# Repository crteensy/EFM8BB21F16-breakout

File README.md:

# EFM8BB21F16-breakout
A simple breakout board for the EFM8BB21F16 (QFN-20) MCU

The silkscreen might be misleading, clarification below the picture:

The bottom row (starting with Vin) ends with 0.2, 0.1, 0.0, Gnd to the right.
The 4-pin connector located towards the center of the board has 3V3, RSTb (C2CK), 2.0 (C2D), Gnd from left to right.

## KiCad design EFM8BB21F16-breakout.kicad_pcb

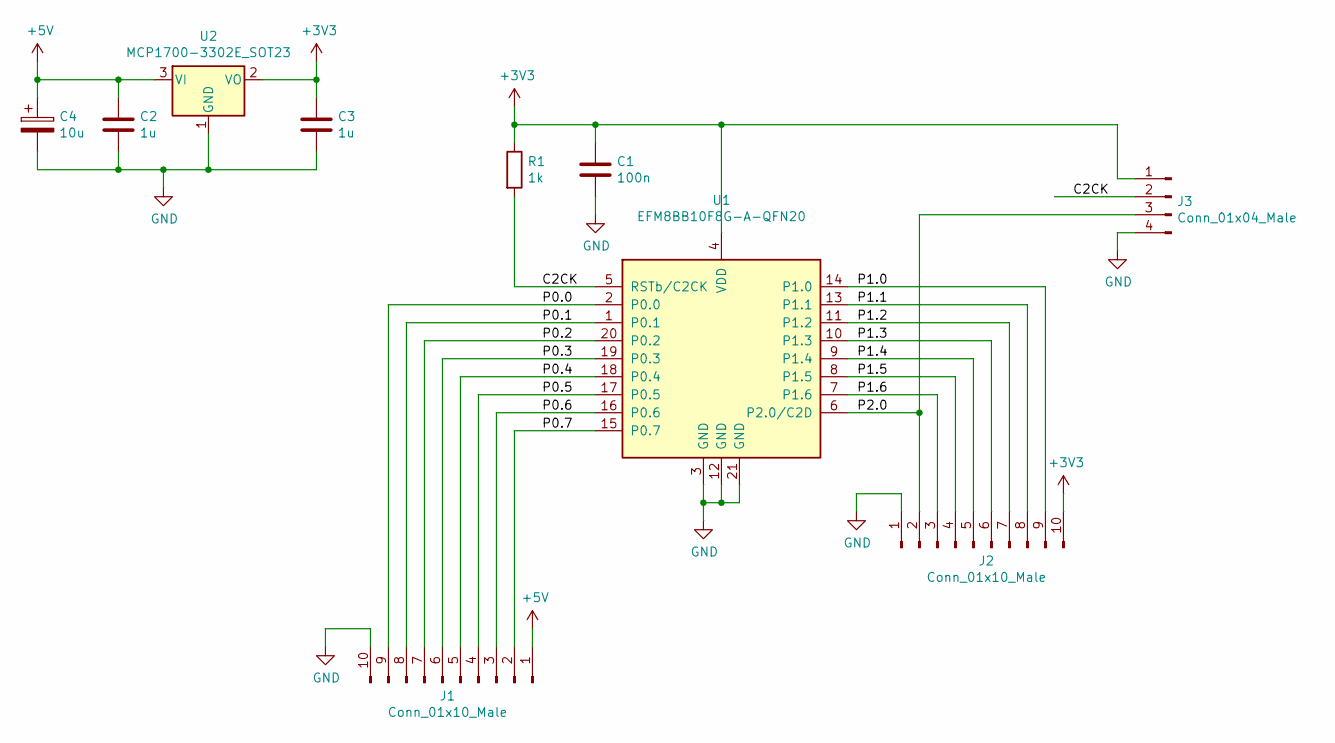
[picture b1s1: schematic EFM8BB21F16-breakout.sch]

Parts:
C1: 100n; C_0603_1608Metric
C2, C3: 1u; C_0603_1608Metric
C4: 10u; C_1206_3216Metric
J1, J2: Conn_01x10_Male; PinHeader_1x10_P2.54mm_Vertical
J3: Conn_01x04_Male; PinHeader_1x04_P2.54mm_Vertical
R1: 1k; R_0603_1608Metric
U1: EFM8BB10F8G-A-QFN20; SiliconLabs_QFN-20-1EP_3x3mm_P0.5mm_ThermalVias
U2: MCP1700-3302E_SOT23; SOT-23

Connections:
+3V3: C1.1, C3.1, J2.10, J3.1, R1.1, U1.4 (VDD), U2.2 (VO)
+5V: C2.1, C4.1, J1.1, U2.3 (VI)
/C2CK: J3.2, R1.2, U1.5 (RSTb/C2CK)
/P0.0: J1.9, U1.2 (P0.0)
/P0.1: J1.8, U1.1 (P0.1)
/P0.2: J1.7, U1.20 (P0.2)
/P0.3: J1.6, U1.19 (P0.3)
/P0.4: J1.5, U1.18 (P0.4)
/P0.5: J1.4, U1.17 (P0.5)
/P0.6: J1.3, U1.16 (P0.6)
/P0.7: J1.2, U1.15 (P0.7)
/P1.0: J2.9, U1.14 (P1.0)
/P1.1: J2.8, U1.13 (P1.1)
/P1.2: J2.7, U1.11 (P1.2)
/P1.3: J2.6, U1.10 (P1.3)
/P1.4: J2.5, U1.9 (P1.4)
/P1.5: J2.4, U1.8 (P1.5)
/P1.6: J2.3, U1.7 (P1.6)
/P2.0: J2.2, J3.3, U1.6 (P2.0/C2D)
GND: C1.2, C2.2, C3.2, C4.2, J1.10, J2.1, J3.4, U1.3 (GND), U1.12 (GND), U1.21 (GND), U2.1 (GND)

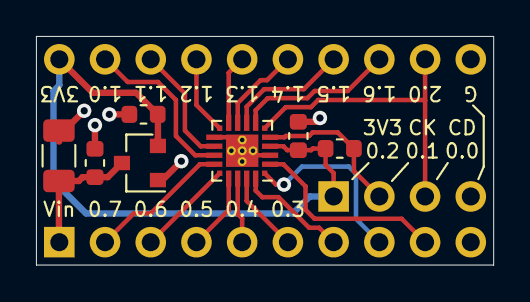
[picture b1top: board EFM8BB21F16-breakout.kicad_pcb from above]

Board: 2 copper layers, 25.4 x 12.7 mm, 10 parts (0 on the bottom side), 20 nets.

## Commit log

2021-01-28 initial bulk
2021-01-28 Update README.md
    typo
2021-01-30 update gitignore
